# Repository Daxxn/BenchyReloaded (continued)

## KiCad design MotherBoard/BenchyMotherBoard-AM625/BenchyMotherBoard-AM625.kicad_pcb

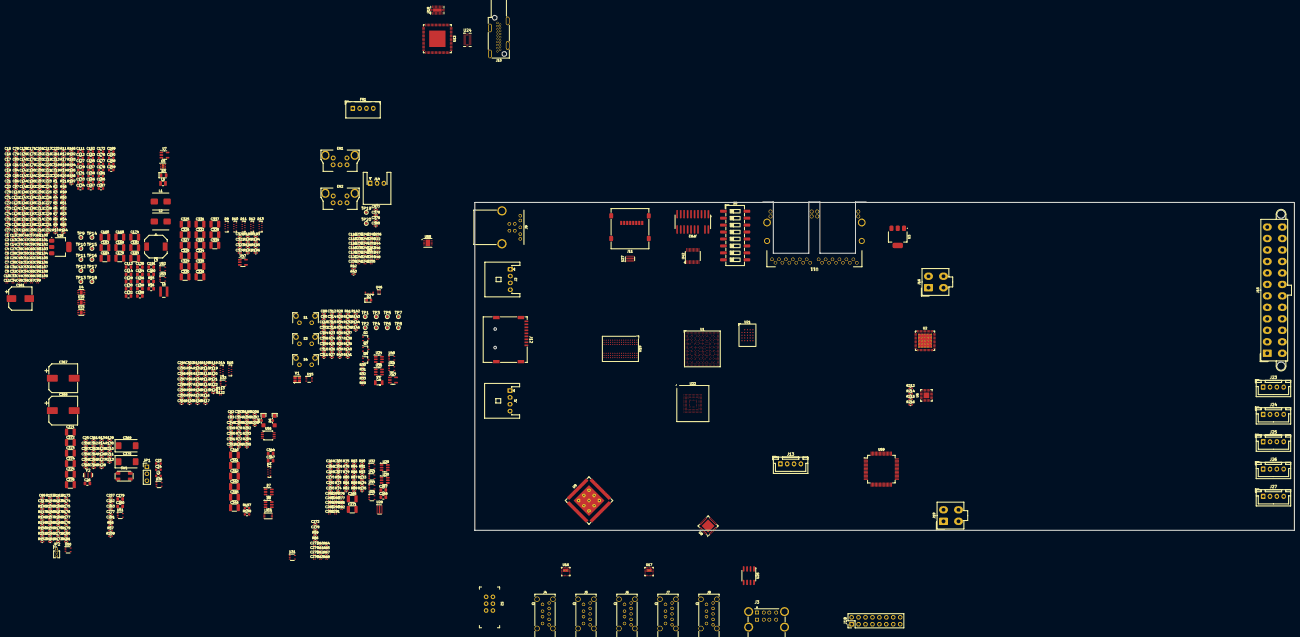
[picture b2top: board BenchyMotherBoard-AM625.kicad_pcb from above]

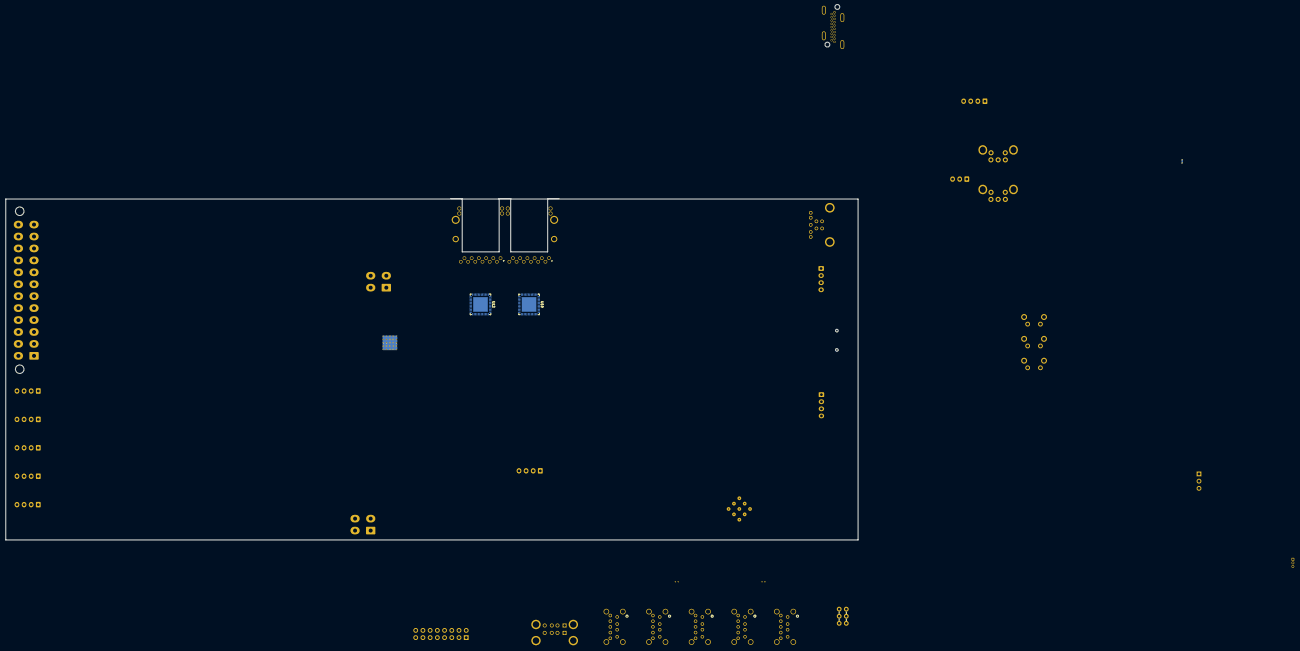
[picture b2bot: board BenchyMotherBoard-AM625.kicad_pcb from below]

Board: 6 copper layers, 300.0 x 120.0 mm, 730 parts (2 on the bottom side), 534 nets, no tracks yet.

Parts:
C1, C2, C3, C4, C5, C6, C7, C8, C9, C255, C256: 1u; CAP_0201
C10, C11, C12, C13, C14, C27, C28, C29, C30, C31, C32, C33, C34, C35, C36, C37, C38, C39, C40, C41, C42, C43, C44, C45, C46, C47, C48, C49, C50, C51, C52, C53, C54, C55, C56, C57, C58, C59, C60, C61, C62, C63, C64, C65, C66, C67, C68, C69, C91, C92, C93, C94, C95, C96, C97, C98, C99, C100, C101, C102, C103, C104, C105, C106, C107, C108, C109, C116, C117, C118, C119, C120, C121, C234, C235, C236, C237, C238, C239, C240, C241, C242, C243, C244, C245, C246, C247, C248, C249, C250, C251, C252, C253, C254, C273, C274, C275, C276, C282, C283, C284, C285, C286, C287, C288, C289, C290, C291: 100n; CAP_0201
C15, C17, C25, C261, C278, C292: 4u7; CAP_0402
C16: 10u; CAP_0402
C18, C19, C20, C21, C82, C83, C87, C88, C89, C90, C110, C115, C122, C123, C124, C125, C126, C136, C137, C138, C139, C140, C141, C142, C143, C144, C145, C146, C147, C148, C150, C151, C162, C165, C171, C173, C175, C179, C180, C184, C185, C192, C193, C194, C195, C196, C197, C198, C199, C200, C201, C202, C203, C204, C205, C206, C207, C208, C209, C210, C211, C212, C213, C214, C215, C216, C217, C218, C219, C220, C221, C222, C223, C224, C225, C226, C227, C228, C229, C230, C231, C232, C257, C262, C263, C264, C266, C269, C270, C272, C277, C281, C293, C294, C295, C296, C297, C298, C299, C300, C301, C302, C303, C304, C305, C306, C307, C308, C309, C310, C311, C312, C313, C314, C315, C316, C317, C319, C321, C322, C323, C324, C348, C349, C350, C351, C352, C354, C355, C357, C358, C359, C360, C361, C362, C363, C364, C365, C366, C377, C378, C379, C380: 100n; CAP_0402
C22, C70, C71, C72, C73: 6n8; CAP_0402
C23, C24, C111, C112, C127, C129, C131, C133, C134, C152, C153, C155, C157, C158, C167, C172, C176, C181, C186, C187, C189, C190, C258, C259: 1u; CAP_0603
C26, C113, C114, C128, C130, C132, C135, C154, C156, C188, C191, C260: 2u2; CAP_0805
C74, C75, C76, C77, C78, C79, C80, C81: 00; CAP_0402
C84, C85, C86, C320: 2n; CAP_0402
C149: 22p; CAP_0402
C159, C267, C268, C279, C280, C344, C347: 10u; CAP_0805
C160, C163, C164, C182, C183, C265, C271, C325, C326, C327, C328, C329, C330, C331, C332, C333, C334, C335, C336, C337, C338, C339, C340, C341, C342, C343, C345, C346, C375, C376: 47u; CAP_1210
C161: 220u; CAP_EL_8x10
C166, C177, C178: 10u; CAP_0603
C168, C169, C170, C174: 100u; CAP_1210
C233, C318: 10n; CAP_0402
C353: 1u; CAP_0402
C356: 2u2; CAP_0402
C367, C368: 220u; CAP_EL_10x10
C369, C370: 47u; CAP_TAN_2917
C371, C372: 22u; CAP_1210
C373, C374: 10u; CAP_1210
D1: EASV3015RGBA0
D2: CZ1-0603-BLUE; LED_0603_1608Metric
D3: APHCM2012SURCK-F01; LED_0805
D4, D9, D10, D11, D12, D13, D14, D15: DT1240A-08LP3810-7; U-DFN3810-9
D5, D6: SM1204SGC; LTST-S321TBKT
D7, D8: USBLC6-4SC6Y; SOT-23-6
EN1, EN2: PEC12R-2220F-S0024; PEC12R
FN1: CFM-5015CF-160-374-22; B4B-XH-A
J1, J2: S4B-XA-SK
J3: 5787745-2
J4, J5, J6, J7, J8: GSB4116341HR
J9: GSB3211311WEU
J10: HD01-19-RA-TH
J11: 472192001
J12: MEM2075-00-140-01-A; MEM2075-00-140-01-A_GCT
J13, J23, J24, J25, J26, J27: B4B-XH-AM; JST_XH_B4B-XH-A_1x04_P2.50mm_Vertical
J14: S3B-XH-A
J15: ATX-0039299243; 0039299243
J16: ATX-0039293046; 0039293046
J18: FRONT PANEL; PinHeader_2x08_P2.54mm_Vertical
J19: 0039293046
JP1: BOOT Jumper; PinHeader_1x03_P2.54mm_Vertical
JP2: Jumper_3_Bridged12; PinHeader_1x03_P1.27mm_Vertical
JPR2: JTAG-CTI; FTR-110-51-L-D-06
L1, L2: 15u; ETQP4MxxxKFN
L3: 8u2; 1217AS-H-8R2M=P3
L4: 100n; IND_0603
L5: 2u2; IND_0806
L6: 3u3; L_Wuerth_MAPI-4030
Q2, Q3, Q4: NX6008NBKWX; SOT-323_SC-70
R1: 750K; RES_0402
R2, R4, R6, R8: 240K; RES_0402
R3: 15K; RES_0402
R5: 300K; RES_0402
R7, R215: 120K; RES_0402
R9, R10, R11, R12, R21, R26, R29, R34, R35, R38, R54, R58, R59, R93, R94, R107, R108, R109, R110, R111, R112, R115, R116, R117, R118, R119, R120, R125, R126, R130, R131, R132, R133, R134, R135, R136, R137, R138, R139, R140, R141, R142, R143, R144, R146, R182, R183, R184, R185, R186, R187, R191, R192, R193, R194, R195, R196, R199, R203, R204, R205, R208, R209, R211, R213: 10K; RES_0402
R13: 3K6; RES_0402
R14, R165: 2K2; RES_0402
R15, R16: 3K3; RES_0805
R17, R18, R19, R20: 00; RES_0402
R22, R44: 240 0.1%; RES_0201
R23, R24, R25, R37, R98, R100, R102, R104, R145, R149, R150, R151, R152, R153, R154, R155, R166, R168, R170, R172, R174, R176, R178, R180, R200, R202: 1K; RES_0402
R27, R28, R36, R210: 100; RES_0402
R30, R31, R32, R33, R62, R64, R65, R68, R69, R76, R77, R85, R92, R113, R122: 22; RES_0201
R39, R41, R147, R148: 22; RES_0402
R40: 0; RES_0402
R42, R43: 39.2 0.1%; RES_0402
R45, R49, R51, R52, R66, R86, R128, R156, R157, R158, R159, R160, R161, R162, R163, R164, R167, R169, R171, R173, R175, R177, R179, R181, R189, R190: 100K; RES_0402
R46, R47, R48: 1K 0.1%; RES_0201
R50: 130K; RES_0402
R53: 110K; RES_0402
R55: 220K; RES_0402
R56, R114, R121: 4K7; RES_0402
R57: 4K3; RES_0402
R60, R61: 1K; RES_0201
R63, R67: 10K; RES_0201
R70: 43K2; RES_0402
R71, R73, R74, R75: 49K9; RES_0402
R72, R188: 12K 0.1%; RES_0402
R78, R79, R80, R81, R82, R83, R84, R87, R88, R89, R90, R91, R201: 47K; RES_0402
R95, R96, R105, R106: 220; RES_0402
R97, R99, R101, R103: 3K3; RES_0402
R123, R124: 4K99; RES_0402
R127: 8K2; RES_0402
R129: 33K; RES_0402
R197, R198: 500 0.1%; RES_0603
R206, R207: 200K; RES_0402
R212: 85K; RES_0402
R214: 122K; RES_0402
R216: 86K; RES_0402
S1, S3, S4: TL1105SF250Q; TL1105SF
S2: PBH2UEESNPNAGX
S5: 219-8MSTR
SW1: TL3365AF180QG
TP1: TP-LPM-EN; TestPoint_Pad_D1.0mm
TP2: TP-SOC-RST-OUT; TestPoint_Pad_D1.0mm
TP3: TP-REF-CLK0; TestPoint_Pad_D1.0mm
TP4: TP-MCU-RST-OUT; TestPoint_Pad_D1.0mm
TP5: TP-MCU-ERR; TestPoint_Pad_D1.0mm
TP6: TP-JTAG-RST; TestPoint_Pad_D1.0mm
TP7: TP-POR-OUT; TestPoint_Pad_D1.0mm
TP8: TP-GLOBAL-RST; TestPoint_Pad_D1.0mm
TP9: TP-HARD-RST; TestPoint_Pad_D1.0mm
TP10: TP-PSEQ-RST; TestPoint_Pad_D1.0mm
TP11: TP-GLOBAL-PG; TestPoint_Pad_D1.0mm
TP12: TP-MAIN-PG; TestPoint_Pad_D1.0mm
TP13: TP-PERP-PG; TestPoint_Pad_D1.0mm
TP14: TP-SOC-PWR-EN; TestPoint_Pad_D1.0mm
TP15: TP-PSEQ-EN1; TestPoint_Pad_D1.0mm
TP16: TP-PSEQ-EN2; TestPoint_Pad_D1.0mm
TP17: TP-PSEQ-EN3; TestPoint_Pad_D1.0mm
TP18: TP-PSEQ-EN4; TestPoint_Pad_D1.0mm
TP19: TP-MI2C-SCL; TestPoint_Pad_D1.0mm
TP20: TP-MI2C-SDA; TestPoint_Pad_D1.0mm
U1: AM6254ATCGGAALW; ALW0425A-BGA-425-13x13mm
U2: TPS65400RGZT; VQFN-48-1EP_7x7mm_P0.5mm_EP5.15x5.15mm_ThermalVias
U3: LM317-JCET; SOT-223
U4: AP3401DNTR-G1; DFN-6-1EP_2x2mm_P0.65mm_EP1x1.6mm
U5: TLV75518PDRVR; WSON-6-1EP_2x2mm_P0.65mm_EP1x1.6mm_ThermalVias
U6: MAX16043TG+T; TQFN-24-1EP_4x4mm_P0.5mm_EP2.1x2.1mm
U7: TPS7A0225PDBVR; SOT-23-5
U8: USB2412-DZK-TR; QFN-28-1EP_5x5mm_P0.5mm_EP3.35x3.35mm
U9: USB7206C/KDX; VQFN-100_EP_12x12_Pitch0.4mm
U10, U12: KSZ9021RN; QFN-48-1EP_7x7mm_P0.5mm_EP5.15x5.15mm
U11: RJMG212S21130ER
U13: SII9022ACNU; QFN-72-1EP_10x10mm_P0.5mm_EP6x6mm
U14: 74LVC1G17GV,125; SOT-23-5
U15: LMK1C1104DQFR; WSON-8_2x2mm_P0.5mm
U16, U17: UCS2114T-1-V/LX; UCS2114T-1-V_LXVAO-Custom
U18: 74LVC541ABQ,115; DHVQFN-20
U19: MT40A1G16TB-062E:F; DDR_FBGA-96_9x13mm_P0.8mm
U20, U23: TLV75901PDRVR; DFN-6-1EP_2x2mm_P0.65mm_EP1x1.6mm
U21: S28HS512TGABHI010; BGA-24_5x5_6.0x8.0mm
U22: EMMC256-TY29-5B101; LFBGA-153_11.5x13mm_Layout14x14_P0.5mm
U24: TPD12S016RKTR; UQFN-24_4x2mm_P0.5mm
U25: AP2156SG-13; SOIC-8_3.9x4.9mm_P1.27mm
U26: AZ1117IH-5.0TRG1; SOT-223
U27, U28: IP4252CZ16-8-TTL; QFN16_SOT1168-1_NEX-M
U29, U30: SIP32510DT-T1-GE3; TSOT-23-6
U31, U32, U33, U43, U44, U45, U48, U49, U50, U51, U52, U53: 74LVC1G08GW,125; SOT-353_SC-70-5
U34, U35: TMP100NA/3K; SOT-23-6
U36: SN74LVC1G17DCKR; SOT-353_SC-70-5
U42: SN74HCS541DGSR; VSSOP20_DGS_TEX
U46: 74LVC3G17GS,115; X2SON-8_1.4x1mm_P0.35mm
U47: AP2171WG-7; SOT-23-5
U55: W25Q16JVUXIQ TR; USON-8_2x3mm_P0.5mm
U56: 74HC2G08DP,125; TSSOP-8_3x3mm_P0.65mm
U58: NCV7357MW3R2G; DFN-8-1EP_3x3mm_P0.5mm_EP1.66x2.38mm
U59: STM32F412RGT6; LQFP-64_10x10mm_P0.5mm
X1: 32.768KHz; Crystal_SMD_3215-2Pin_3.2x1.5mm
Y1: 25MHz; Crystal_SMD_4Pin_2.5x2.0mm
Y2: 16MHz; Resonator_SMD_3Pin_3.0x1.1mm

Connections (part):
+12V: C159.1, C160.1, C161.1 (+), C259.1, C260.1, C367.1 (+), C368.1 (+), C369.1, C370.1, FN1.1 (V+), J1.1, J15.10 (12V1), J15.11 (12V1), J16.3 (12V), J16.4 (12V), J19.3, J23.1, J24.1, J25.1, J26.1, J27.1, R55.1, R129.1, U2.5 (PVIN1), U2.6 (PVIN2), U2.22 (VIN), U2.30 (PVIN3), U2.31 (PVIN4), U26.3 (IN)
-12V: J15.14 (-12), J19.4
/DDR MEMORY/DDR-A0: U1.J1 (DDR0-A0), U19.P3 (A0)
/DDR MEMORY/DDR-A1: U1.J2 (DDR0-A1), U19.P7 (A1)
/DDR MEMORY/DDR-A2: U1.K3 (DDR0-A2), U19.R3 (A2)
/DDR MEMORY/DDR-A3: U1.L5 (DDR0-A3), U19.N7 (A3)
/DDR MEMORY/DDR-A4: U1.K4 (DDR0-A4), U19.N3 (A4)
/DDR MEMORY/DDR-A5: U1.K1 (DDR0-A5), U19.P8 (A5)
/DDR MEMORY/DDR-A6: U1.R2 (DDR0-A6), U19.P2 (A6)
/DDR MEMORY/DDR-A7: U1.P2 (DDR0-A7), U19.R8 (A7)
/DDR MEMORY/DDR-A8: U1.P1 (DDR0-A8), U19.R2 (A8)
/DDR MEMORY/DDR-A9: U1.P4 (DDR0-A9), U19.R7 (A9)
/DDR MEMORY/DDR-A10: U1.R5 (DDR0-A10), U19.M3 (A10/AP)
/DDR MEMORY/DDR-A11: U1.P5 (DDR0-A11), U19.T2 (A11)
/DDR MEMORY/DDR-A12: U1.R6 (DDR0-A12), U19.M7 (A12/~BC)
/DDR MEMORY/DDR-A13: U1.R1 (DDR0-A13), U19.T8 (A13)
/DDR MEMORY/DDR-BA0: U1.M1 (DDR0-BA0), U19.N2 (BA0)
/DDR MEMORY/DDR-BA1: U1.N1 (DDR0-BA1), U19.N8 (BA1)
/DDR MEMORY/DDR-BG0: U1.T4 (DDR0-BG0), U19.M2 (BG0)
/DDR MEMORY/DDR-CKE: U1.H2 (DDR0-CKE0), U19.K2 (CKE)
/DDR MEMORY/DDR-CLK+: R42.1, U1.L1 (DDR0-CK0+), U19.K7 (CK+)
/DDR MEMORY/DDR-CLK-: R43.1, U1.L2 (DDR0-CK0-), U19.K8 (CK-)
/DDR MEMORY/DDR-DM0: U1.H5 (DDR0-DM0), U19.E7 (~LDM)
/DDR MEMORY/DDR-DM1: U1.W5 (DDR0-DM1), U19.E2 (~UDM)
/DDR MEMORY/DDR-DQ0: U1.F4 (DDR0-DQ0), U19.G2 (DQ0)
/DDR MEMORY/DDR-DQ1: U1.G5 (DDR0-DQ1), U19.F7 (DQ1)
/DDR MEMORY/DDR-DQ2: U1.F3 (DDR0-DQ2), U19.H3 (DQ2)
/DDR MEMORY/DDR-DQ3: U1.H6 (DDR0-DQ3), U19.H7 (DQ3)
/DDR MEMORY/DDR-DQ4: U1.E3 (DDR0-DQ4), U19.H2 (DQ4)
/DDR MEMORY/DDR-DQ5: U1.G2 (DDR0-DQ5), U19.H8 (DQ5)
/DDR MEMORY/DDR-DQ6: U1.F2 (DDR0-DQ6), U19.J3 (DQ6)
/DDR MEMORY/DDR-DQ7: U1.F1 (DDR0-DQ7), U19.J7 (DQ7)
/DDR MEMORY/DDR-DQ8: U1.U1 (DDR0-DQ8), U19.A3 (DQ8)
/DDR MEMORY/DDR-DQ9: U1.U3 (DDR0-DQ9), U19.B8 (DQ9)
/DDR MEMORY/DDR-DQ10: U1.U2 (DDR0-DQ10), U19.C3 (DQ10)
/DDR MEMORY/DDR-DQ11: U1.V5 (DDR0-DQ11), U19.C7 (DQ11)
/DDR MEMORY/DDR-DQ12: U1.W2 (DDR0-DQ12), U19.C2 (DQ12)
/DDR MEMORY/DDR-DQ13: U1.V6 (DDR0-DQ13), U19.C8 (DQ13)
/DDR MEMORY/DDR-DQ14: U1.Y1 (DDR0-DQ14), U19.D3 (DQ14)
/DDR MEMORY/DDR-DQ15: U1.W1 (DDR0-DQ15), U19.D7 (DQ15)
/DDR MEMORY/DDR-DQS0+: U1.E1 (DDR0-DQS0+), U19.G3 (LDQS+)
/DDR MEMORY/DDR-DQS0-: U1.E2 (DDR0-DQS0-), U19.F3 (LDQS-)
/DDR MEMORY/DDR-DQS1+: U1.V1 (DDR0-DQS1+), U19.B7 (UDQS+)
/DDR MEMORY/DDR-DQS1-: U1.V2 (DDR0-DQS1-), U19.A7 (UDQS-)
/DDR MEMORY/DDR-ODT: U1.H1 (DDR0-ODT0), U19.K3 (ODT)
/DDR MEMORY/DDR-PAR: U1.T1 (DDR0-PAR), U19.T3 (PAR)
/DDR MEMORY/DDR-~ACT: U1.N6 (DDR0-~ACT), U19.L3 (~ACT)
/DDR MEMORY/DDR-~ALERT: U1.R3 (DDR0-~ALERT), U19.P9 (~ALERT)
/DDR MEMORY/DDR-~CAS: U1.M4 (DDR0-~CAS), U19.M8 (~CAS/A15)
/DDR MEMORY/DDR-~CS: U1.L6 (DDR0-~CS0), U19.L7 (~CS)
/DDR MEMORY/DDR-~RAS: U1.M5 (DDR0-~RAS), U19.L8 (~RAS/A16)
/DDR MEMORY/DDR-~RESET: U1.G1 (DDR0-~RESET0), U19.P1 (~RESET)
/DDR MEMORY/DDR-~WE: U1.N3 (DDR0-~WE), U19.L2 (~WE/A14)
/DDR MEMORY/VREF-DDR: C116.2, C117.2, C118.1, C119.1, R46.2, R47.1, U19.M1 (VREFCA)
/DISPLAY/DSS-D0: U1.U22 (VOUT0-DATA0), U13.32 (D0)
/DISPLAY/DSS-D1: U1.V24 (VOUT0-DATA1), U13.31 (D1)
/DISPLAY/DSS-D2: U1.W25 (VOUT0-DATA2), U13.30 (D2)
/DISPLAY/DSS-D3: U1.W24 (VOUT0-DATA3), U13.29 (D3)
/DISPLAY/DSS-D4: U1.Y25 (VOUT0-DATA4), U13.28 (D4)
/DISPLAY/DSS-D5: U1.Y24 (VOUT0-DATA5), U13.27 (D5)
/DISPLAY/DSS-D6: U1.Y23 (VOUT0-DATA6), U13.25 (D6)
/DISPLAY/DSS-D7: U1.AA25 (VOUT0-DATA7), U13.24 (D7)
/DISPLAY/DSS-D8: U1.V21 (VOUT0-DATA8), U13.23 (D8)
/DISPLAY/DSS-D9: U1.W21 (VOUT0-DATA9), U13.20 (D9)
/DISPLAY/DSS-D10: U1.V20 (VOUT0-DATA10), U13.19 (D10)
/DISPLAY/DSS-D11: U1.AA23 (VOUT0-DATA11), U13.18 (D11)
/DISPLAY/DSS-D12: U1.AB25 (VOUT0-DATA12), U13.17 (D12)
/DISPLAY/DSS-D13: U1.AA24 (VOUT0-DATA13), U13.16 (D13)
/DISPLAY/DSS-D14: U1.Y22 (VOUT0-DATA14), U13.15 (D14)
/DISPLAY/DSS-D15: U1.AA21 (VOUT0-DATA15), U13.14 (D15)
/DISPLAY/DSS-DCLK: U1.AC24 (VOUT0-PCLK), U13.22 (IDCK)
/DISPLAY/DSS-DE: U1.Y20 (VOUT0-DE), U13.33 (DE)
/DISPLAY/DSS-HSYNC: U1.AB24 (VOUT0-HSYNC), U13.34 (HSYNC)
/DISPLAY/DSS-VSYNC: U1.AC25 (VOUT0-VSYNC), U13.35 (VSYNC)
/DISPLAY/HDMI-TX0+: J10.7 (D0+), U13.62 (TX0+), U24.17 (D0+)
/DISPLAY/HDMI-TX0-: J10.9 (D0-), U13.61 (TX0-), U24.16 (D0-)
/DISPLAY/HDMI-TX1+: J10.4 (D1+), U13.65 (TX1+), U24.20 (D1+)
/DISPLAY/HDMI-TX1-: J10.6 (D1-), U13.64 (TX1-), U24.19 (D1-)
/DISPLAY/HDMI-TX2+: J10.1 (D2+), U13.68 (TX2+), U24.22 (D2+)
/DISPLAY/HDMI-TX2-: J10.3 (D2-), U13.67 (TX2-), U24.21 (D2-)
/DISPLAY/HDMI-TXC+: J10.10 (CK+), U13.59 (TXC+), U24.15 (CLK+)
/DISPLAY/HDMI-TXC-: J10.12 (CK-), U13.58 (TXC-), U24.14 (CLK-)
/DISPLAY/RESET-HDMI: R209.1, U13.51 (~RESET), U51.4 (Y)
/EMMC/RESET-EMMC: R93.1, U22.K5 (~RESET), U32.4 (Y)
/EMMC/SD0-CLK: R73.1, R92.2, U22.M6 (CLK)
/EMMC/SD0-CMD: R75.2, U1.Y3 (MMC0-CMD), U22.M5 (CMD)
/EMMC/SD0-D0: R74.2, U1.AA2 (MMC0-DAT0), U22.A3 (D0)
/EMMC/SD0-D1: U1.AA1 (MMC0-DAT1), U22.A4 (D1)
/EMMC/SD0-D2: U1.AA3 (MMC0-DAT2), U22.A5 (D2)
/EMMC/SD0-D3: U1.Y4 (MMC0-DAT3), U22.B2 (D3)
/EMMC/SD0-D4: U1.AB2 (MMC0-DAT4), U22.B3 (D4)
/EMMC/SD0-D5: U1.AC1 (MMC0-DAT5), U22.B4 (D5)
/EMMC/SD0-D6: U1.AD2 (MMC0-DAT6), U22.B5 (D6)
/EMMC/SD0-D7: U1.AC2 (MMC0-DAT7), U22.B6 (D7)
/EMMC/SD1-CLK: R76.2, R83.1, U27.4 (4A)
/EMMC/SD1-CMD: R80.2, U1.A21 (MMC1-CMD), U27.3 (3A)
/EMMC/SD1-D0: R81.2, U1.A22 (MMC1-DAT0), U27.5 (5A)
/EMMC/SD1-D1: R84.2, U1.B21 (MMC1-DAT1), U27.6 (6A)
/EMMC/SD1-D2: R78.2, U1.C21 (MMC1-DAT2), U27.1 (1A)
/EMMC/SD1-D3: R79.2, U1.D22 (MMC1-DAT3), U27.2 (2A)
/EMMC/SD1-PWR: R134.2, U29.3 (EN), U43.4 (Y)
/EMMC/SD1-PWR-EN: U1.C17 (GPIO1-49), U43.2 (A)
/EMMC/SD2-CLK: R77.2, R89.1, U28.4 (4A)
/EMMC/SD2-CMD: R87.2, U1.C24 (MMC2-CMD), U28.3 (3A)
/EMMC/SD2-D0: R82.2, U1.B24 (MMC2-DAT0), U28.5 (5A)
/EMMC/SD2-D1: R91.2, U1.C25 (MMC2-DAT1), U28.6 (6A)
/EMMC/SD2-D2: R90.2, U1.E23 (MMC2-DAT2), U28.1 (1A)
/EMMC/SD2-D3: R88.2, U1.D24 (MMC2-DAT3), U28.2 (2A)
/EMMC/SD2-DET: R86.2, U1.A23 (MMC2-SDCD), U28.7 (7A)
/EMMC/SD2-PWR: R135.2, U1.B23 (GPIO0-72), U30.3 (EN), U44.4 (Y)
/EMMC/SDCARD-EXT-RESET: R133.2, U43.1 (B), U44.1 (B), U45.4 (Y)
/ETHERNET/ETH-PHY1-A+: D14.1 (K1), U11.B1 (MD1+), U12.2 (TXRX-A+)
/ETHERNET/ETH-PHY1-A-: D14.2 (K2), U11.B2 (MD1-), U12.3 (TXRX-A-)
/ETHERNET/ETH-PHY1-B+: D14.4 (K3), U11.B4 (MD2+), U12.5 (TXRX-B+)
/ETHERNET/ETH-PHY1-B-: D14.5 (K4), U11.B5 (MD2-), U12.6 (TXRX-B-)
/ETHERNET/ETH-PHY1-C+: D14.6 (K5), U11.B7 (MD3+), U12.7 (TXRX-C+)
/ETHERNET/ETH-PHY1-C-: D14.7 (K6), U11.B8 (MD3-), U12.8 (TXRX-C-)
/ETHERNET/ETH-PHY1-D+: D14.8 (K7), U11.B10 (MD4+), U12.10 (TXRX-D+)
/ETHERNET/ETH-PHY1-D-: D14.9 (K8), U11.B11 (MD4-), U12.11 (TXRX-D-)
/ETHERNET/ETH-PHY2-A+: D15.9 (K8), U10.2 (TXRX-A+), U11.A1 (MD1+)
/ETHERNET/ETH-PHY2-A-: D15.8 (K7), U10.3 (TXRX-A-), U11.A2 (MD1-)
/ETHERNET/ETH-PHY2-B+: D15.7 (K6), U10.5 (TXRX-B+), U11.A4 (MD2+)
/ETHERNET/ETH-PHY2-B-: D15.6 (K5), U10.6 (TXRX-B-), U11.A5 (MD2-)
/ETHERNET/ETH-PHY2-C+: D15.5 (K4), U10.7 (TXRX-C+), U11.A7 (MD3+)
/ETHERNET/ETH-PHY2-C-: D15.4 (K3), U10.8 (TXRX-C-), U11.A8 (MD3-)
/ETHERNET/ETH-PHY2-D+: D15.2 (K2), U10.10 (TXRX-D+), U11.A10 (MD4+)
/ETHERNET/ETH-PHY2-D-: D15.1 (K1), U10.11 (TXRX-D-), U11.A11 (MD4-)
/ETHERNET/MDIO-MDC: U1.AD24 (MDIO0-MDC), U10.36 (MD-SCL), U12.36 (MD-SCL)
/ETHERNET/MDIO-MDIO: U1.AB22 (MDIO0-MDIO), U10.37 (MD-SDA), U12.37 (MD-SDA)
/ETHERNET/RESET-ETH: R94.2, U10.42 (~RESET), U12.42 (~RESET), U33.4 (Y)
/ETHERNET/RGMII1-GTX-CLK: U1.AE19 (RGMII1-TXC), U12.24 (GTX-CLK)
/ETHERNET/RGMII1-RXCLK: R115.2, R122.1, U1.AD17 (RGMII1-RXC)
/ETHERNET/RGMII1-RXD0: R117.2, U1.AB17 (RGMII1-RD0), U12.32 (RXD0/_{MODE0})
/ETHERNET/RGMII1-RXD1: R118.2, U1.AC17 (RGMII1-RD1), U12.31 (RXD1/_{MODE1})
/ETHERNET/RGMII1-RXD2: R119.2, U1.AB16 (RGMII1-RD2), U12.28 (RXD2/_{MODE2})
/ETHERNET/RGMII1-RXD3: R120.2, U1.AA15 (RGMII1-RD3), U12.27 (RXD3/_{MODE3})
/ETHERNET/RGMII1-RXDV: R116.2, U1.AE17 (RGMII1-RX-CTL), U12.33 (RX-DV/_{CLK125-EN})
/ETHERNET/RGMII1-TXD0: U1.AE20 (RGMII1-TD0), U12.19 (TXD0)
/ETHERNET/RGMII1-TXD1: U1.AD20 (RGMII1-TD1), U12.20 (TXD1)
/ETHERNET/RGMII1-TXD2: U1.AE18 (RGMII1-TD2), U12.21 (TXD2)
/ETHERNET/RGMII1-TXD3: U1.AD18 (RGMII1-TD3), U12.22 (TXD3)
/ETHERNET/RGMII1-TXEN: U1.AD19 (RGMII1-TX-CTL), U12.25 (TX-EN)
/ETHERNET/RGMII2-GTX-CLK: U1.AE21 (RGMII2-TXC), U10.24 (GTX-CLK)
/ETHERNET/RGMII2-RXCLK: R112.2, R113.1, U1.AD23 (RGMII2-RXC)
/ETHERNET/RGMII2-RXD0: R110.2, U1.AE23 (RGMII2-RD0), U10.32 (RXD0/_{MODE0})
/ETHERNET/RGMII2-RXD1: R109.2, U1.AB20 (RGMII2-RD1), U10.31 (RXD1/_{MODE1})
/ETHERNET/RGMII2-RXD2: R108.2, U1.AC21 (RGMII2-RD2), U10.28 (RXD2/_{MODE2})
/ETHERNET/RGMII2-RXD3: R107.2, U1.AE22 (RGMII2-RD3), U10.27 (RXD3/_{MODE3})
/ETHERNET/RGMII2-RXDV: R111.2, U1.AD22 (RGMII2-RX-CTL), U10.33 (RX-DV/_{CLK125-EN})
/ETHERNET/RGMII2-TXD0: U1.Y18 (RGMII2-TD0), U10.19 (TXD0)
/ETHERNET/RGMII2-TXD1: U1.AA18 (RGMII2-TD1), U10.20 (TXD1)
/ETHERNET/RGMII2-TXD2: U1.AD21 (RGMII2-TD2), U10.21 (TXD2)
/ETHERNET/RGMII2-TXD3: U1.AC20 (RGMII2-TD3), U10.22 (TXD3)
/ETHERNET/RGMII2-TXEN: U1.AA19 (RGMII2-TX-CTL), U10.25 (TX-EN)
/POWER DISTRIBUTION/3V3-SENSE: R210.2, R213.1, U59.16 (ADC1-IN2)
/POWER DISTRIBUTION/5V-SENSE: R127.2, R211.1, U59.15 (ADC1-IN1)
/POWER DISTRIBUTION/12V-SENSE: R129.2, R130.1, U59.14 (ADC1-IN0)
/POWER DISTRIBUTION/BOOT: R125.1, U59.60 (BOOT0)
/POWER DISTRIBUTION/FP-DISP-CIPO: J18.5, U59.22 (SPI1-CIPO)
/POWER DISTRIBUTION/FP-DISP-COPI: J18.7, U59.23 (SPI1-COPI)
/POWER DISTRIBUTION/FP-DISP-CS: J18.9, U59.26 (PB0)
/POWER DISTRIBUTION/FP-DISP-DC: J18.11, U59.27 (PB1)
/POWER DISTRIBUTION/FP-DISP-RESET: J18.1, U59.20 (PA4)
/POWER DISTRIBUTION/FP-DISP-SCLK: J18.3, U59.21 (SPI1-SCK)
/POWER DISTRIBUTION/FP-IND-ERROR: J18.6, U59.39 (PC8)
/POWER DISTRIBUTION/FP-IND-STATUS: J18.4, U59.38 (PC7)
/POWER DISTRIBUTION/FP-SYS-PWR-SW: C365.1, J18.13, R128.2, U36.2 (A)
/POWER DISTRIBUTION/PWR-RESET: R126.2, SW1.1, U59.7 (RESET)
/POWER DISTRIBUTION/SMPS-EN: J15.16 (PS-ON), U59.11 (PC3)
/POWER DISTRIBUTION/SMPS-PG: J15.8 (PWR-OK), U59.10 (PC2)
/POWER DISTRIBUTION/SYS-PWR-SW: U36.4 (Y), U59.24 (PC4)
/POWER/MAIN-PGOOD: R12.2, TP12.1 (TP), U2.17 (PGOOD), U53.2 (A)
/POWER/PERIP-PGOOD: TP13.1 (TP), U4.2 (PG), U53.1 (B)
/POWER/PSEQ-EN1: R187.2, TP15.1 (TP), U2.48 (ENSW1/ENSEQ), U6.9 (EN2), U6.17 (OUT1)
/POWER/PSEQ-EN2: R186.2, TP16.1 (TP), U2.27 (ENSW3), U4.1 (EN), U6.10 (EN3), U6.16 (OUT2), U20.4 (EN), U23.4 (EN)
/POWER/PSEQ-EN3: R185.2, TP17.1 (TP), U2.34 (ENSW4), U6.11 (EN4), U6.15 (OUT3), U7.3 (EN)
/POWER/PSEQ-EN4: R184.2, TP18.1 (TP), U2.13 (ENSW2), U6.14 (OUT4)
/POWER/PSEQ-RESET: R164.1, TP10.1 (TP), U6.18 (~RESET), U52.1 (B)
/POWER/VDD-CORE-SEQ: R212.2, R214.1, U6.5 (IN4)
/POWER/VDD-DDR-SEQ: R215.2, R216.1, U6.4 (IN3)
/SOC CONTROL/CONN-JTAG-RESET: JPR2.15 (~RESET), R142.2, U42.4 (A3)
/SOC CONTROL/JTAG-EMU0: JPR2.13 (EMU0), U42.18 (Y1)
/SOC CONTROL/JTAG-EMU1: JPR2.14 (EMU1), U42.17 (Y2)
/SOC CONTROL/JTAG-RESET: R143.2, TP6.1 (TP), U42.16 (Y3), U48.2 (A)
/SOC CONTROL/JTAG-TCK: JPR2.11 (TCK), R139.2, U42.9 (A8)
/SOC CONTROL/JTAG-TDI: JPR2.3 (TDI), R136.2, U42.8 (A7)
/SOC CONTROL/JTAG-TDO: JPR2.7 (TDO), U42.13 (Y6)
/SOC CONTROL/JTAG-TMS: JPR2.1 (TMS), R140.2, U42.6 (A5)
/SOC CONTROL/JTAG-TRST: JPR2.2 (~TRST), R141.1, U42.5 (A4)
/SOC CONTROL/MCU-ERROR: R28.2, TP5.1 (TP), U1.D1 (MCU-~ERROR)
/SOC CONTROL/MCU-POR: R131.1, U1.D2 (~MCU-POR), U48.4 (Y)
/SOC CONTROL/MCU-RESET-OUT: R36.1, TP4.1 (TP), U1.B12 (MCU-~RESET-STAT)
/SOC CONTROL/MCU-RESET-SW: U1.E11 (MCU-~RESET), U46.7 (1Y)
/SOC CONTROL/POWER-SW: C314.1, R26.2, S2.2 (COM1), U14.2 (A)
/SOC CONTROL/SOC-EMU0: R138.2, U1.E12 (EMU0), U42.2 (A1)
/SOC CONTROL/SOC-EMU1: R137.2, U1.C11 (EMU1), U42.3 (A2)
/SOC CONTROL/SOC-MCU-CLK: R33.2, U1.B2 (MCU-OSC0-XI)
/SOC CONTROL/SOC-SLEEP-SW: U1.B3 (MCU-MCAN0-RX), U46.2 (3Y)
/SOC CONTROL/SOC-TCK: R39.2, U42.11 (Y8)
/SOC CONTROL/SOC-TDI: U1.A11 (TDI), U42.12 (Y7)
/SOC CONTROL/SOC-TDO: R41.2, U42.7 (A6)
/SOC CONTROL/SOC-TMS: U1.B11 (TMS), U42.14 (Y5)
/SOC CONTROL/SOC-TRST: U1.B10 (~TRST), U42.15 (Y4)
/SOC CONTROL/SOFT-RESET-SW: U1.F20 (~RESET-REQ), U46.5 (2Y)
/SOC GPIO/CAN+: C379.1, J14.1, U58.7 (CANH)
/SOC GPIO/CAN-: C380.2, J14.3, U58.6 (CANL)
/SOC GPIO/FAN-PWM: FN1.4 (PWM), U1.E18 (EHRPWM1-B)
/SOC GPIO/RELAY1: R170.2, R171.1, U1.M25 (GPIO0-15)
/SOC GPIO/RELAY2: R168.2, R169.1, U1.N23 (GPIO0-16)
/SOC GPIO/RELAY3: R166.2, R167.1, U1.N24 (GPIO0-17)
/SOC GPIO/RELAY4: R156.1, S5.1 (1A), U1.N25 (GPIO0-18)
/SOC GPIO/RELAY5: R157.1, S5.2 (2A), U1.P24 (GPIO0-19)
/SOC GPIO/RELAY6: R158.1, S5.3 (3A), U1.P22 (GPIO0-20)
/SOC GPIO/RELAY7: R159.1, S5.4 (4A), U1.P21 (GPIO0-21)
/SOC GPIO/RELAY8: R160.1, S5.5 (5A), U1.R23 (GPIO0-22)
/SOC GPIO/WKUP-UART-RX: J2.3, U1.B4 (WKUP-UART0-RXD)
/SOC GPIO/WKUP-UART-TX: J2.2, U1.C5 (WKUP-UART0-TXD)
/SPI FLASH MEMORY/FLASH-CLK: R62.1, R66.1, U21.B2 (CK)
/SPI FLASH MEMORY/FLASH-CS: R67.2, U1.F23 (OSPI0-~CS0), U21.C2 (~CS)
/SPI FLASH MEMORY/FLASH-D0: U1.E25 (OSPI0-D0), U21.D3 (DQ0)
/SPI FLASH MEMORY/FLASH-D1: U1.G24 (OSPI0-D1), U21.D2 (DQ1)
/SPI FLASH MEMORY/FLASH-D2: U1.F25 (OSPI0-D2), U21.C4 (DQ2)
/SPI FLASH MEMORY/FLASH-D3: U1.F24 (OSPI0-D3), U21.D4 (DQ3)
/SPI FLASH MEMORY/FLASH-D4: U1.J23 (OSPI0-D4), U21.D5 (DQ4)
/SPI FLASH MEMORY/FLASH-D5: U1.J25 (OSPI0-D5), U21.E3 (DQ5)
/SPI FLASH MEMORY/FLASH-D6: U1.H25 (OSPI0-D6), U21.E2 (DQ6)
/SPI FLASH MEMORY/FLASH-D7: U1.J22 (OSPI0-D7), U21.E1 (DQ7)
/SPI FLASH MEMORY/FLASH-DS: R60.2, R61.1, R64.1, R65.1, U21.C3 (DS)
/SPI FLASH MEMORY/FLASH-INT: R63.2, U1.H21 (GPIO0-13), U21.A5 (~INT)
/SPI FLASH MEMORY/FLASH-RESET: U1.E24 (OSPI0-RESET-OUT0), U31.2 (A)
/SPI FLASH MEMORY/RESET-FLASH: R59.2, U21.A4 (~RESET), U31.4 (Y)
/SPI FLASH MEMORY/SOC-FLASH-DQS: R64.2, U1.J24 (OSPI0-DQS)
/SPI FLASH MEMORY/SOC-FLASH-LBCLK: R65.2, R68.1
/USB/HUB-FL-CS: U9.69 (~SPI_CE), U55.1 (~CS)
/USB/HUB-FL-D0: U9.70 (SPI-D0), U55.5 (IO0)
/USB/HUB-FL-D1: U9.71 (SPI-D1), U55.2 (IO1)
/USB/HUB-FL-D2: U9.72 (SPI-D2), U55.3 (IO2)
/USB/HUB-FL-D3: U9.73 (SPI-D3), U55.7 (IO3)
/USB/HUB-FL-SLCK: U9.68 (SPI-SCLK), U55.6 (CLK)
/USB/RESET-HUB-USB: U9.1 (~RESET), U56.7 (1Y)
/USB/RESET-SOC-USB: U8.17 (~RESET), U56.3 (2Y)
/USB/SOC-USB1-D+: D7.1 (IO1), D7.6 (IO4), J3.A3 (D1+), U8.1 (USBD1-D+)
/USB/SOC-USB1-D-: D7.3 (IO2), D7.4 (IO3), J3.A2 (D1-), U8.28 (USBD1-D-)
/USB/SOC-USB2-D+: D8.1 (IO1), D8.6 (IO4), J3.B3 (D2+), U8.3 (USBD2-D+)
/USB/SOC-USB2-D-: D8.3 (IO2), D8.4 (IO3), J3.B2 (D2-), U8.2 (USBD2-D-)
/USB/SOC-USB-D+: U1.AD11 (USB0-D+), U9.42 (USBD6-D+)
/USB/SOC-USB-D-: U1.AE11 (USB0-D-), U9.41 (USBD6-D-)
/USB/SOC-USB-OCS1: U8.8 (OCS1), U25.2 (~FLG1)
/USB/SOC-USB-OCS2: U8.12 (OCS2), U25.3 (~FLG2)
/USB/SOC-USB-PWEN1: U8.7 (PRTPWR1), U25.1 (EN1)
/USB/SOC-USB-PWEN2: U8.11 (PRTPWR2), U25.4 (EN2)
/USB/USB HUB PORTS/USBD1-D+: D9.1 (K1), J4.2 (D-), U9.5 (USBD1-D+)
/USB/USB HUB PORTS/USBD1-D-: D9.2 (K2), J4.3 (D+), U9.6 (USBD1-D-)
/USB/USB HUB PORTS/USBD1-RX+: D9.4 (K3), J4.5 (SSRX-), U9.10 (USBD1-RX+)
/USB/USB HUB PORTS/USBD1-RX-: D9.7 (K6), J4.6 (SSRX+), U9.11 (USBD1-RX-)
/USB/USB HUB PORTS/USBD1-TX+: D9.8 (K7), J4.8 (SSTX-), U9.7 (USBD1-TX+)
/USB/USB HUB PORTS/USBD1-TX-: D9.9 (K8), J4.9 (SSTX+), U9.8 (USBD1-TX-)
/USB/USB HUB PORTS/USBD2-D+: D10.1 (K1), J7.2 (D-), U9.14 (USBD2-D+)
/USB/USB HUB PORTS/USBD2-D-: D10.2 (K2), J7.3 (D+), U9.15 (USBD2-D-)
/USB/USB HUB PORTS/USBD2-RX+: D10.4 (K3), J7.5 (SSRX-), U9.19 (USBD2-RX+)
/USB/USB HUB PORTS/USBD2-RX-: D10.7 (K6), J7.6 (SSRX+), U9.20 (USBD2-RX-)
/USB/USB HUB PORTS/USBD2-TX+: D10.8 (K7), J7.8 (SSTX-), U9.16 (USBD2-TX+)
/USB/USB HUB PORTS/USBD2-TX-: D10.9 (K8), J7.9 (SSTX+), U9.17 (USBD2-TX-)
/USB/USB HUB PORTS/USBD3-D+: D11.1 (K1), J5.2 (D-), U9.27 (USBD3-D+)
/USB/USB HUB PORTS/USBD3-D-: D11.2 (K2), J5.3 (D+), U9.28 (USBD3-D-)
/USB/USB HUB PORTS/USBD3-RX+: D11.4 (K3), J5.5 (SSRX-), U9.32 (USBD3-RX+)
/USB/USB HUB PORTS/USBD3-RX-: D11.7 (K6), J5.6 (SSRX+), U9.33 (USBD3-RX-)
/USB/USB HUB PORTS/USBD3-TX+: D11.8 (K7), J5.8 (SSTX-), U9.29 (USBD3-TX+)
/USB/USB HUB PORTS/USBD3-TX-: D11.9 (K8), J5.9 (SSTX+), U9.30 (USBD3-TX-)
/USB/USB HUB PORTS/USBD4-D+: D12.1 (K1), J6.2 (D-), U9.34 (USBD4-D+)
/USB/USB HUB PORTS/USBD4-D-: D12.2 (K2), J6.3 (D+), U9.35 (USBD4-D-)
/USB/USB HUB PORTS/USBD4-RX+: D12.4 (K3), J6.5 (SSRX-), U9.39 (USBD4-RX+)
/USB/USB HUB PORTS/USBD4-RX-: D12.7 (K6), J6.6 (SSRX+), U9.40 (USBD4-RX-)
/USB/USB HUB PORTS/USBD4-TX+: D12.8 (K7), J6.8 (SSTX-), U9.36 (USBD4-TX+)
/USB/USB HUB PORTS/USBD4-TX-: D12.9 (K8), J6.9 (SSTX+), U9.37 (USBD4-TX-)
/USB/USB HUB PORTS/USBD5-D+: D13.1 (K1), J8.2 (D-), U9.81 (USBD5-D+)
/USB/USB HUB PORTS/USBD5-D-: D13.2 (K2), J8.3 (D+), U9.82 (USBD5-D-)
/USB/USB HUB PORTS/USBD5-RX+: D13.4 (K3), J8.5 (SSRX-), U9.86 (USBD5-RX+)
/USB/USB HUB PORTS/USBD5-RX-: D13.7 (K6), J8.6 (SSRX+), U9.87 (USBD5-RX-)
/USB/USB HUB PORTS/USBD5-TX+: D13.8 (K7), J8.8 (SSTX-), U9.83 (USBD5-TX+)
/USB/USB HUB PORTS/USBD5-TX-: D13.9 (K8), J8.9 (SSTX+), U9.84 (USBD5-TX-)
/USB/USB-OCP1: R194.2, U9.60 (PORT-CTRL1), U16.1 (EN1), U16.20 (ALERT1)
/USB/USB-OCP2: R193.2, U9.59 (PORT-CTRL2), U16.15 (EN2), U16.16 (ALERT2)
/USB/USB-OCP3: R196.2, U9.58 (PORT-CTRL3), U17.1 (EN1), U17.20 (ALERT1)
/USB/USB-OCP4: R195.2, U9.57 (PORT-CTRL4), U17.15 (EN2), U17.16 (ALERT2)
/USB/USB-OCP5: U9.56 (PORT-CTRL5), U47.3 (~FLG), U47.4 (EN)
/USB/USB-SOC-VBUS: U1.F18 (USB1-DRVVBUS), U8.18 (VBUS-DET)
/USB/USBP-D+: D4.1 (K1), J9.3 (D+), U9.89 (USBU-D+)
/USB/USBP-D-: D4.2 (K2), J9.2 (D-), U9.90 (USBU-D-)
/USB/USBP-RX+: D4.8 (K7), J9.9 (SSRX+), U9.94 (USBU-RX+)
/USB/USBP-RX-: D4.9 (K8), J9.8 (SSRX-), U9.95 (USBU-RX-)
/USB/USBP-TX+: D4.4 (K3), J9.6 (SSTX+), U9.91 (USBU-TX+)
/USB/USBP-TX-: D4.7 (K6), J9.5 (SSTX-), U9.92 (USBU-TX-)
/USB/USP-VBUS: J9.1 (VBUS), R70.1
/USB/USP-VBUS-DET: R70.2, R71.1, U9.2 (VBUS-MON)
DSS-D16: U1.R24 (VOUT0-DATA16), U13.13 (D16), U18.18 (Y0)
DSS-D17: U1.R25 (VOUT0-DATA17), U13.11 (D17), U18.17 (Y1)
DSS-D18: U1.T25 (VOUT0-DATA18), U13.10 (D18), U18.16 (Y2)
DSS-D19: U1.R21 (VOUT0-DATA19), U13.9 (D19), U18.15 (Y3)
DSS-D20: U1.T22 (VOUT0-DATA20), U13.8 (D20), U18.14 (Y4)
DSS-D21: U1.T24 (VOUT0-DATA21), U13.7 (D21), U18.13 (Y5)
DSS-D22: U1.U25 (VOUT0-DATA22), U13.6 (D22), U18.12 (Y6)
DSS-D23: U1.U24 (VOUT0-DATA23), U13.4 (D23), U18.11 (Y7)
ETH1-MCLK: R32.2, U12.46 (XI)
ETH2-MCLK: R31.2, U10.46 (XI)
ETH-INT: U1.D16 (EXTINTn), U10.38 (~INT), U12.38 (~INT)
GLOBAL-PGOOD: R165.2, R183.1, TP11.1 (TP), U52.2 (A), U53.4 (Y), U59.8 (GPIO-EXTI0)
GLOBAL-RESET: R146.1, TP8.1 (TP), U31.1 (B), U33.1 (B), U45.2 (A), U49.4 (Y), U51.2 (A), U56.1 (1A), U56.5 (2A)
GND: C1.2, C2.2, C3.2, C4.2, C5.2, C6.2, C7.2, C8.2, C9.2, C10.2, C11.2, C12.2, C13.2, C14.2, C15.2, C16.2, C17.2, C22.2, C23.2, C24.2, C25.2, C26.2, C27.2, C28.2, C29.2, C30.2, C31.2, C32.2, C33.2, C34.2, C35.2, C36.2, C37.2, C38.2, C39.2, C40.2, C41.2, C42.2, C43.2, C44.2, C45.2, C46.2, C47.2, C48.2, C49.2, C50.2, C51.2, C52.2, C53.2, C54.2, C55.2, C56.2, C57.2, C58.2, C59.2, C60.2, C61.2, C62.2, C63.2, C64.2, C65.2, C66.2, C67.2, C68.2, C69.2, C70.1, C71.1, C72.1, C73.1, C74.1, C75.1, C76.1, C77.1, C78.1, C79.1, C80.1, C81.1, C82.2, C83.2, C84.1, C85.1, C86.1, C87.2, C88.2, C89.1, C90.2, C91.2, C92.2, C93.2, C94.2, C95.2, C96.2, C97.2, C98.2, C99.2, C100.2, C101.2, C102.2, C103.2, C104.2, C105.2, C106.2, C107.2, C108.2, C109.2, C110.1, C111.2, C112.2, C113.2, C114.2, C115.2, C118.2, C119.2, C120.2, C121.2, C122.2, C123.2, C124.2, C125.2, C126.2, C127.2, C128.2, C129.2, C130.2, C131.2, C132.2, C133.2, C134.2, C135.2, C136.2, C137.2, C138.2, C139.2, C140.2, C141.2, C142.2, C143.2, C144.2, C145.2, C146.2, C147.2, C148.2, C150.2, C151.2, C152.2, C153.2, C154.2, C155.2, C156.2, C157.2, C158.2, C159.2, C160.2, C161.2 (-), C162.2, C163.2, C164.2, C165.2, C166.2, C167.2, C168.2, C169.2, C170.2, C171.2, C172.2, C173.2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
HARD-RESET: R182.1, TP9.1 (TP), U48.1 (B), U52.4 (Y)
MAIN-I2C-SCL: TP19.1 (TP), U1.B17 (I2C1-SCL), U13.1 (CSCL), U16.19 (I2C-SCLK), U17.19 (I2C-SCLK), U34.1 (SCL), U35.1 (SCL)
MAIN-I2C-SDA: TP20.1 (TP), U1.A17 (I2C1-SDA), U13.2 (CSDA), U16.18 (I2C-SDA), U17.18 (I2C-SDA), U34.6 (SDA), U35.6 (SDA)
MCU-SPI-CS: U1.A13 (SPI0-CS0), U59.33 (SPI2-~SS)
MCU-SPI-SCLK: U1.A14 (SPI0-CLK), U59.34 (SPI2-SCK)
MCU-SPI-SDI: U1.B14 (SPI0-DI), U59.35 (SPI2-CIPO)
MCU-SPI-SDO: U1.B13 (SPI0-DO), U59.36 (SPI2-COPI)
unnamed: C18.2, L3.1, U2.2 (SW1), U2.3 (SW1), U2.4 (SW1)
unnamed: C19.2, L6.1, U2.9 (SW2), U2.10 (SW2), U2.11 (SW2)
unnamed: C74.2, R17.1
unnamed: C77.2, R18.1
unnamed: C79.2, R19.1
unnamed: C81.2, R20.1
unnamed: C120.1, R42.2, R43.2
unnamed: D1.2 (B), R23.1
unnamed: D1.3 (G), R24.1
unnamed: D1.4 (R), R25.1
unnamed: D2.1 (K), R37.1
unnamed: D3.1 (K), R165.1
unnamed: D5.2 (A), U8.16 (HS-IND)
unnamed: D5.1 (K), R200.1
unnamed: D6.2 (A), R201.1, U8.19 (SUSP-IND/NON-REM0)
unnamed: D6.1 (K), R202.1
unnamed: C342.1, C343.1, J3.A1 (VBUS1), U25.8 (OUT1)
unnamed: C340.1, C341.1, J3.B1 (VBUS2), U25.5 (OUT2)
unnamed: C326.1, J4.1 (VBUS), U16.4 (VBUS1), U16.5 (VBUS1)
unnamed: C333.1, J5.1 (VBUS), U17.4 (VBUS1), U17.5 (VBUS1)
unnamed: C336.1, J6.1 (VBUS), U17.11 (VBUS2), U17.12 (VBUS2)
unnamed: C330.1, J7.1 (VBUS), U16.11 (VBUS2), U16.12 (VBUS2)
unnamed: C337.1, J8.1 (VBUS), U47.1 (OUT)
unnamed: C262.1, C263.1, J10.18 (+5V), U24.12 (5V-OUT)
unnamed: J10.13 (CEC), U24.6 (CEC-B)
unnamed: J10.19 (HPD), U24.9 (HPD-B)
unnamed: J10.15 (SCL), U24.7 (SCL-B)
unnamed: J10.16 (SDA), U24.8 (SDA-B)
unnamed: J11.5 (CLK), U27.13 (4B)
unnamed: J11.3 (CMD), U27.14 (3B)
unnamed: J11.7 (DAT0), U27.12 (5B)
unnamed: J11.8 (DAT1), U27.11 (6B)
unnamed: J11.1 (DAT2), U27.16 (1B)
unnamed: J11.2 (DAT3/CD), U27.15 (2B)
unnamed: C264.1, C265.1, J11.4 (VDD), R78.1, R79.1, R80.1, R81.1, R84.1, U29.1 (OUT), U29.2 (OUT)
unnamed: J12.5 (CLK), U28.13 (4B)
unnamed: J12.3 (CMD), U28.14 (3B)
unnamed: J12.7 (DAT0), U28.12 (5B)
unnamed: J12.8 (DAT1), U28.11 (6B)
unnamed: J12.1 (DAT2), U28.16 (1B)
unnamed: J12.2 (DAT3/CD), U28.15 (2B)
unnamed: J12.9 (DET), U28.10 (7B)
unnamed: C270.1, C271.1, J12.4 (VDD), U30.1 (OUT), U30.2 (OUT)
unnamed: JP1.2 (C), R125.2
unnamed: JP2.2 (C), U50.2 (A)
unnamed: JPR2.4 (TDIS), R40.1
unnamed: Q2.3 (D), R25.2
unnamed: Q2.1 (G), R28.1
unnamed: Q3.3 (D), R24.2
unnamed: Q3.1 (G), R27.1
unnamed: Q4.3 (D), R37.2
unnamed: Q4.1 (G), R36.2, R38.1
unnamed: R82.1, R86.1, R87.1, R88.1, R90.1, R91.1
unnamed: R95.2, U11.AL2 (LED-K)
unnamed: R96.2, U11.AL4 (LED-K)
unnamed: R105.2, U11.BL2 (LED-K)
unnamed: R106.2, U11.BL4 (LED-K)
unnamed: R23.2, S2.5 (COM2)
unnamed: R145.2, S5.16 (1B)
unnamed: R149.2, S5.15 (2B)
unnamed: R150.2, S5.14 (3B)
unnamed: R151.2, S5.13 (4B)
unnamed: R152.2, S5.12 (5B)
unnamed: R161.1, S5.6 (6A), U18.2 (A0)
unnamed: R153.2, S5.11 (6B)
unnamed: R162.1, S5.7 (7A), U18.3 (A1)
unnamed: R154.2, S5.10 (7B)
unnamed: R163.1, S5.8 (8A), U18.4 (A2)
unnamed: R155.2, S5.9 (8B)
unnamed: TP1.1 (TP), U1.B7 (PMIC-LPM-EN0)
unnamed: TP3.1 (TP), U1.A18 (EXT-REFCLK1)
unnamed: C5.1, U1.H15 (CAP-VDDS0)
unnamed: C6.1, U1.K18 (CAP-VDDS1)
unnamed: C7.1, U1.W17 (CAP-VDDS2)
unnamed: C8.1, U1.P19 (CAP-VDDS3)
unnamed: C4.1, U1.U7 (CAP-VDDS4)
unnamed: C3.1, U1.H17 (CAP-VDDS5)
unnamed: C2.1, U1.J19 (CAP-VDDS6)
unnamed: C9.1, U1.G9 (CAP-VDDS-CANUART)
unnamed: C1.1, U1.H11 (CAP-VDDS-MCU)
unnamed: U1.C2 (WKUP-LFOSC0-XI), X1.2
unnamed: U1.C1 (WKUP-LFOSC0-XO), X1.1
unnamed: R39.1, U1.A10 (TCK)
unnamed: R41.1, U1.D12 (TDO)
unnamed: R22.1, U1.M2 (DDR0-CAL0)
unnamed: C233.1, R54.1, R55.2, U1.H10 (VMON-VSYS)
unnamed: R198.1, U1.AE10 (USB0-RCALIB)
unnamed: U1.AE9 (USB1-D+), U8.22 (USBU+)
unnamed: U1.AD10 (USB1-D-), U8.21 (USBU-)
unnamed: R197.1, U1.AC9 (USB1-RCALIB)
unnamed: R62.2, U1.H24 (OSPI0-CLK)
unnamed: R68.2, U1.G25 (OSPI0-LBCLKO)
unnamed: U1.E15 (MCAN0-RX), U58.4 (RX)
unnamed: U1.C15 (MCAN0-TX), U58.1 (TX)
unnamed: U1.E14 (UART0-TXD), U58.8 (S)
unnamed: R92.1, U1.AB1 (MMC0-CLK)
unnamed: R76.1, U1.B22 (MMC1-CLK)
unnamed: R85.1, U1.D17 (MMC1-SDCD)
unnamed: R77.1, U1.D25 (MMC2-CLK)
unnamed: C18.1, U2.1 (CB1)
unnamed: C19.1, U2.12 (CB2)
unnamed: C20.1, U2.28 (CB3)
unnamed: C21.1, U2.33 (CB4)
unnamed: C75.2, R17.2, U2.46 (COMP1)
unnamed: C76.2, R18.2, U2.15 (COMP2)
unnamed: C78.2, R19.2, U2.25 (COMP3)
unnamed: C80.2, R20.2, U2.36 (COMP4)
unnamed: R9.1, U2.38 (I2CADDR)
unnamed: C22.1, R10.1, U2.40 (RCLOCK_SYNC)
unnamed: C70.2, U2.45 (SS1)
unnamed: C71.2, U2.16 (SS2)
unnamed: C72.2, U2.24 (SS3)
unnamed: C73.2, U2.37 (SS4)
unnamed: C20.2, L1.1, U2.29 (SW3)
unnamed: C21.2, L2.1, U2.32 (SW4)
unnamed: C16.1, U2.19 (VDDA)
unnamed: C15.1, U2.20 (VDDD)
unnamed: C17.1, U2.18 (VDDG)
unnamed: R1.2, R2.1, U2.47 (VFB1)
unnamed: R3.2, R4.1, U2.14 (VFB2)
unnamed: R5.2, R6.1, U2.26 (VFB3)
unnamed: R7.2, R8.1, U2.35 (VFB4)
unnamed: R13.2, R14.1, U3.1 (ADJ)
unnamed: C149.2, R51.2, R52.1, U4.6 (FB)
unnamed: L5.1, U4.4 (LX)
unnamed: C320.2, U6.24 (CDLY1)
unnamed: C84.2, U6.23 (CDLY2)
unnamed: C85.2, U6.22 (CDLY3)
unnamed: C86.2, U6.21 (CDLY4)
unnamed: C318.1, U6.20 (CRESET)
unnamed: R21.2, U6.8 (EN1)
unnamed: C82.1, U8.9 (CRFILT)
unnamed: C83.1, U8.25 (PLLFILT)
unnamed: R188.1, U8.26 (RBIAS)
unnamed: R205.1, U9.21 (CFG-STRAP1)
unnamed: R206.1, U9.22 (CFG-STRAP2)
unnamed: R207.1, U9.23 (CFG-STRAP3)
unnamed: R199.2, U9.63 (TEST1)
unnamed: R203.2, U9.64 (TEST2)
unnamed: R204.2, U9.65 (TEST3)
unnamed: R208.1, U9.24 (TESTEN)
unnamed: R72.1, U9.100 (RBIAS)
unnamed: R114.2, U10.41 (CLK125-NDO/_{LED-MODE})
unnamed: R96.1, R97.2, R98.1, U10.17 (LED1/_{PHYAD0})
unnamed: R95.1, R99.2, R100.1, U10.15 (LED2/_{PHYAD1})
unnamed: R113.2, U10.35 (RX-CLK/_{PHYAD2})
unnamed: R123.2, U10.48 (ISET)
unnamed: C295.2, U11.A3 (MDCT1)
unnamed: C296.2, U11.A6 (MDCT2)
unnamed: C297.2, U11.A9 (MDCT3)
unnamed: C298.2, U11.A12 (MDCT4)
unnamed: C299.2, U11.B3 (MDCT1)
unnamed: C300.2, U11.B6 (MDCT2)
unnamed: C301.2, U11.B9 (MDCT3)
unnamed: C302.2, U11.B12 (MDCT4)
unnamed: R121.2, U12.41 (CLK125-NDO/_{LED-MODE})
unnamed: R101.2, R102.1, R106.1, U12.17 (LED1/_{PHYAD0})
unnamed: R103.2, R104.1, R105.1, U12.15 (LED2/_{PHYAD1})
unnamed: R122.2, U12.35 (RX-CLK/_{PHYAD2})
unnamed: R124.2, U12.48 (ISET)
unnamed: R56.1, U13.72 (CI2CA)
unnamed: R57.1, U13.56 (EXT-SWING)
unnamed: U13.71 (CEC-A), U24.24 (CEC-A)
unnamed: U13.49 (DSCL), U24.1 (SCL-A)
unnamed: U13.48 (DSDA), U24.2 (SDA-A)
unnamed: U13.54 (HPD), U24.3 (HPD-A)
unnamed: R69.2, U15.1 (CLK-IN)
unnamed: R33.1, U15.3 (Y0)
unnamed: R32.1, U15.8 (Y1)
unnamed: R31.1, U15.5 (Y2)
unnamed: R30.1, U15.7 (Y3)
unnamed: R192.2, U16.13 (BOOST)
unnamed: R190.1, U16.3 (COMM-EN)
unnamed: R191.2, U17.13 (BOOST)
unnamed: R189.1, U17.3 (COMM-EN)
unnamed: R172.2, R173.1, U18.5 (A3)
unnamed: R174.2, R175.1, U18.6 (A4)
unnamed: R176.2, R177.1, U18.7 (A5)
unnamed: R178.2, R179.1, U18.8 (A6)
unnamed: R180.2, R181.1, U18.9 (A7)
unnamed: U18.1 (~OE1), U18.19 (~OE2), U50.4 (Y)
unnamed: R48.1, U19.N9 (TEN)
unnamed: R44.1, U19.F9 (ZQ)
unnamed: R45.2, R49.1, U20.2 (FB)
unnamed: R58.1, U22.H5 (DS)
unnamed: C286.1, U22.C2 (VDDI)
unnamed: R50.2, R53.1, U23.2 (FB)
unnamed: C310.1, R132.2, S4.1, U46.1 (1A)
unnamed: C309.1, R29.2, S1.1, U46.3 (2A)
unnamed: C311.1, R34.2, S3.1, U46.6 (3A)
unnamed: R147.2, R148.1, U50.1 (B)
unnamed: U59.5 (OSC-IN), Y2.1
unnamed: U59.6 (OSC-OUT), Y2.3
unnamed: C356.1, U59.30 (VCAP1)
unnamed: C363.1, C364.1, L4.2, U59.13 (VREF+)
unnamed: R69.1, Y1.3 (OUT)
unnamed: R144.2, Y1.1 (TRI)
POR-OUT: R148.2, TP7.1 (TP), U1.E21 (~POR-OUT), U49.1 (B)
SOC-PWR-EN: R11.2, TP14.1 (TP), U2.39 (~RESET), U6.19 (~MR), U59.25 (GPIO-EXTI5)
SOC-PWR-SW: R35.1, U14.4 (Y), U59.9 (PC1)
SOC-RESET-OUT: R27.2, R147.1, TP2.1 (TP), U1.F22 (~RESETSTA), U32.1 (B), U45.1 (B), U49.2 (A)
SYS-I2C-SCL: J13.2, R16.2, U1.A8 (MCU-I2C0-SCL), U2.43 (SCL)
SYS-I2C-SDA: J13.3, R15.2, U1.D10 (MCU-I2C0-SDA), U2.42 (SDA)
USB-MCLK: R30.2, U8.24 (XTALIN), U9.98 (CLK_IN)
VCC-HDMI: C258.1, C261.1, C280.1, C281.1, U24.10 (VCC), U26.2 (OUT), U26.4 (OUT)
VCC-STBY: C23.1, C26.1, J15.9 (5V-STBY), J27.3, U3.3 (IN)
VCC-USB: C325.1, C327.1, C328.1, C329.1, C331.1, C332.1, C334.1, C335.1, C338.1, C339.1, C344.1, C345.1, C346.1, C347.1, C371.1, C372.1, C373.1, C374.1, J1.3, J15.4 (5V), J15.6 (5V), J15.21 (5V), J15.22 (5V), J15.23 (5V), J23.3, J24.3, J25.3, J26.3, R127.1, U16.6 (VS), U16.7 (VS), U16.9 (VS), U16.10 (VS), U17.6 (VS), U17.7 (VS), U17.9 (VS), U17.10 (VS), U25.7 (VIN), U47.5 (IN)
VDD: C272.2, C273.1, C274.1, C275.1, C276.1, C278.1, R59.1, R60.1, R63.1, R67.1, U21.B4 (VCC), U21.D1 (VCCQ), U21.E4 (VCCQ), U31.5 (VCC)
VDD-CORE: C35.1, C36.1, C37.1, C38.1, C39.1, C40.1, C41.1, C42.1, C43.1, C44.1, C45.1, C46.1, C47.1, C48.1, C49.1, C91.1, C92.1, C93.1, C94.1, C95.1, C96.1, C97.1, C98.1, C102.1, C103.1, C104.1, C105.1, C106.1, C168.1, C169.1, C170.1, C171.1, C172.1, C173.1, C174.1, L6.2, R3.1, R212.1, U1.F8 (VDD-CANUART), U1.H8 (VDD_CORE), U1.J11 (VDD_CORE), U1.J12 (VDDR-CORE), U1.J14 (VDD_CORE), U1.K16 (VDDR-CORE), U1.K17 (VDD_CORE), U1.L12 (VDD_CORE), U1.L15 (VDD_CORE), U1.M16 (VDD_CORE), U1.N8 (VDD_CORE), U1.N11 (VDD_CORE), U1.N12 (VDDR-CORE), U1.N13 (VDD_CORE), U1.N14 (VDDR-CORE), U1.P16 (VDDR-CORE), U1.P17 (VDD_CORE), U1.R11 (VDD_CORE), U1.R12 (VDDR-CORE), U1.R14 (VDD_CORE), U1.T10 (VDDR-CORE), U1.U12 (VDD_CORE), U1.U14 (VDDR-CORE), U1.V8 (VDD_CORE), U1.V15 (VDD_CORE), U1.V17 (VDD_CORE), U1.W12 (VDDA-CORE-USB), U1.W13 (VDDA-CORE-CSIRX0)
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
